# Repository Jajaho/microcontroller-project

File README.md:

# Projekt Mikrocontroller
Layout and Source code files.  
Uses the PlatformIO IDE in VSCode.  
## Useful links
[C++ Formatter](https://codebeautify.org/cpp-formatter-beautifier)

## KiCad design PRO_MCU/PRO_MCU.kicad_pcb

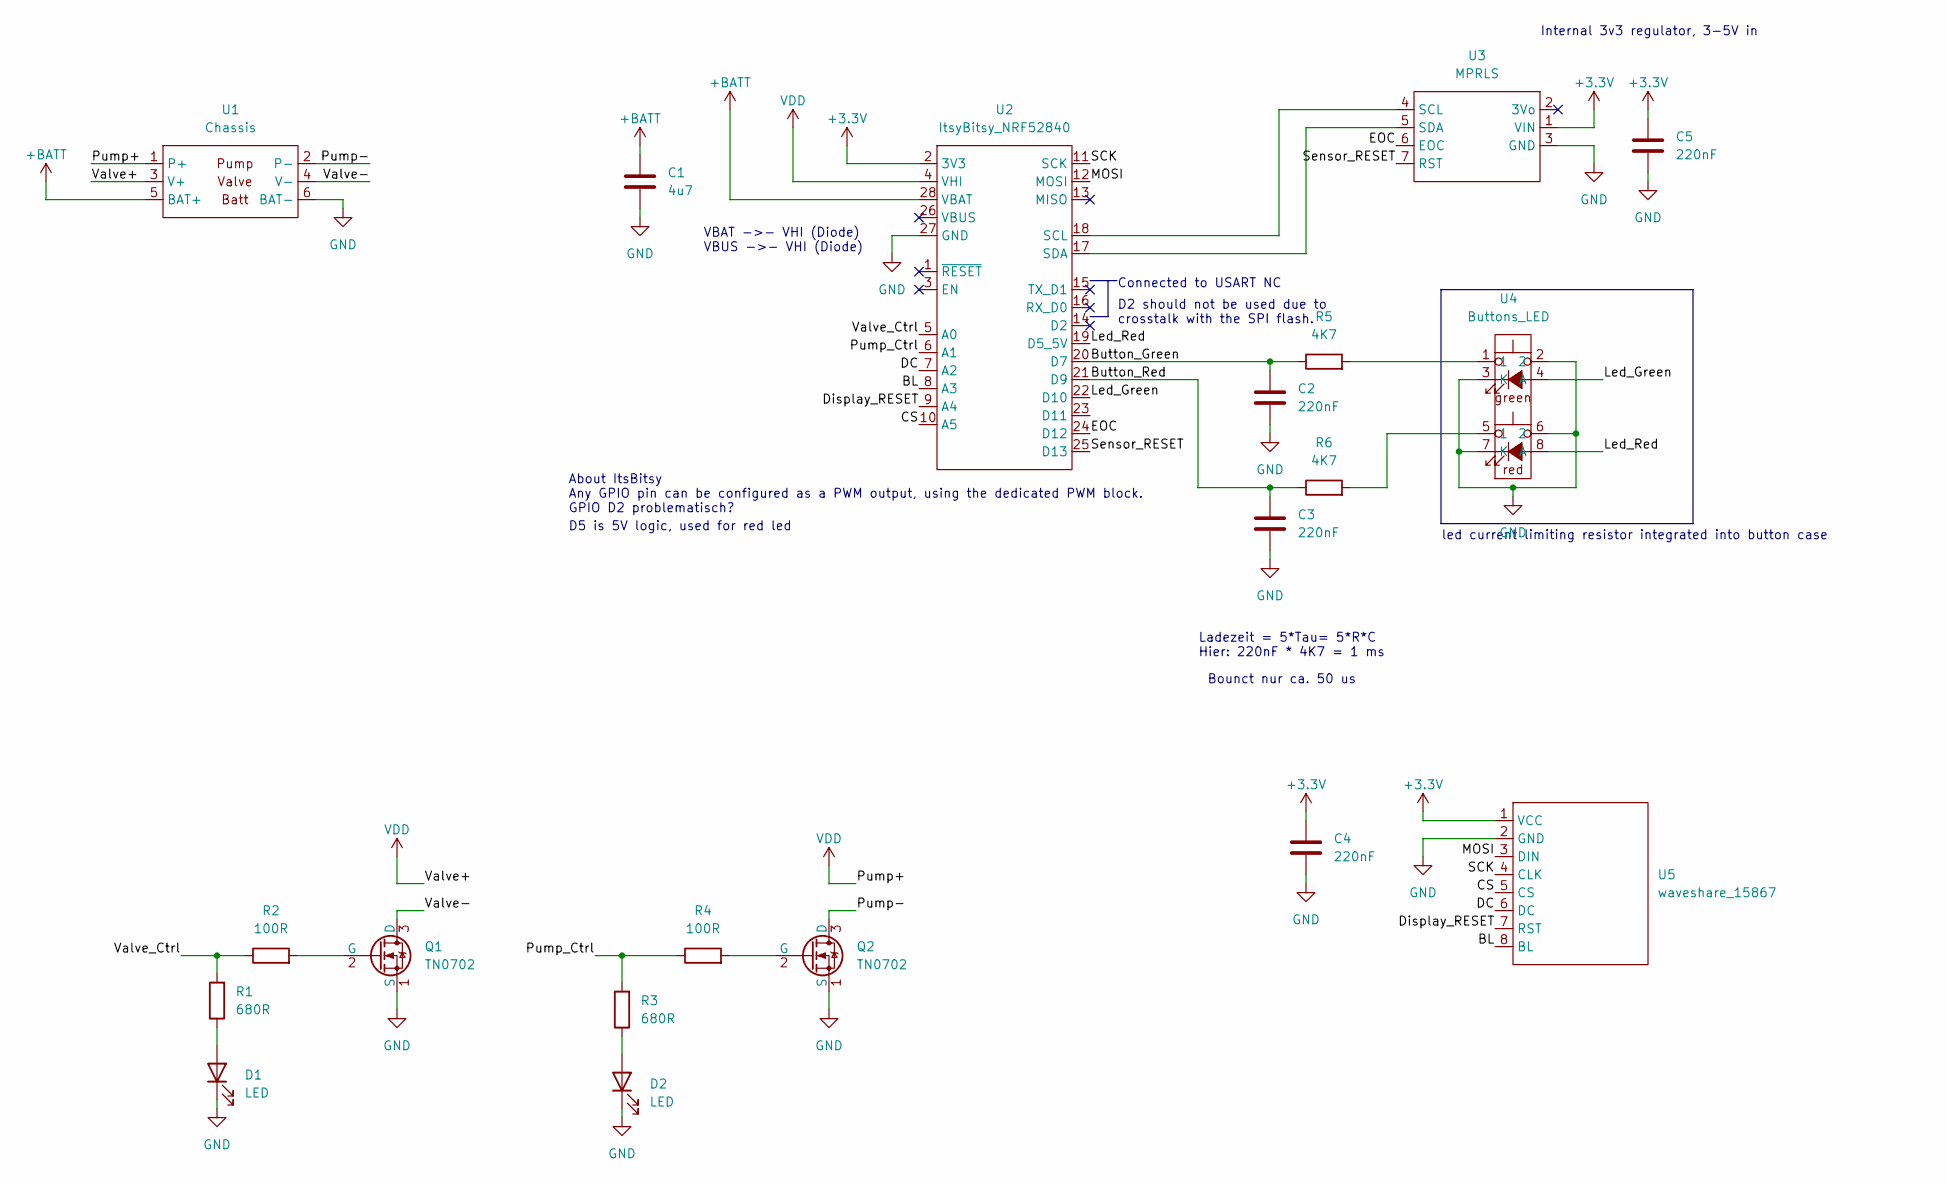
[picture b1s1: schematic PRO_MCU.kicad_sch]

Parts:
C1: 4u7; C_0805_2012Metric_Pad1.18x1.45mm_HandSolder
C2, C3, C4, C5: 220nF; C_0805_2012Metric_Pad1.18x1.45mm_HandSolder
D1, D2: LED; LED_D3.0mm
Q1, Q2: TN0702; TO-92
R1, R3: 680R; R_Axial_DIN0207_L6.3mm_D2.5mm_P10.16mm_Horizontal
R2, R4: 100R; R_Axial_DIN0207_L6.3mm_D2.5mm_P10.16mm_Horizontal
R5, R6: 4K7; R_Axial_DIN0207_L6.3mm_D2.5mm_P10.16mm_Horizontal
U1: Chassis; IDC-Header_2x03_P2.54mm_Vertical
U2: ItsyBitsy_NRF52840
U3: MPRLS
U4: Buttons_LED; IDC-Header_2x04_P2.54mm_Vertical
U5: waveshare_15867; IDC-Header_2x04_P2.54mm_Vertical

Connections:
+3.3V: C4.1, C5.1, U2.2 (3V3), U3.1 (VIN), U5.1 (VCC)
+BATT: C1.1, U1.5 (BAT+), U2.28 (VBAT)
/BL: U2.8 (A3), U5.8 (BL)
/Button_Green: C2.1, R5.1, U2.20 (D7)
/Button_Red: C3.1, R6.1, U2.21 (D9)
/CS: U2.10 (A5), U5.5 (CS)
/DC: U2.7 (A2), U5.6 (DC)
/Display_RESET: U2.9 (A4), U5.7 (RST)
/EOC: U2.24 (D12), U3.6 (EOC)
/Led_Green: U2.22 (D10), U4.4 (A)
/Led_Red: U2.19 (D5_5V), U4.8 (A)
/MOSI: U2.12 (MOSI), U5.3 (DIN)
/Pump-: Q2.3 (D), U1.2 (P-)
/Pump_Ctrl: R3.2, R4.1, U2.6 (A1)
/SCK: U2.11 (SCK), U5.4 (CLK)
/Sensor_RESET: U2.25 (D13), U3.7 (RST)
/Valve-: Q1.3 (D), U1.4 (V-)
/Valve_Ctrl: R1.2, R2.1, U2.5 (A0)
GND: C1.2, C2.2, C3.2, C4.2, C5.2, D1.1 (K), D2.1 (K), Q1.1 (S), Q2.1 (S), U1.6 (BAT-), U2.27 (GND), U3.3 (GND), U4.2, U4.3 (K), U4.6 (2), U4.7 (K), U5.2 (GND)
unnamed: D1.2 (A), R1.1
unnamed: D2.2 (A), R3.1
unnamed: Q1.2 (G), R2.2
unnamed: Q2.2 (G), R4.2
unnamed: R5.2, U4.1
unnamed: R6.2, U4.5 (1)
unnamed: U2.18 (SCL), U3.4 (SCL)
unnamed: U2.17 (SDA), U3.5 (SDA)
VDD: U1.1 (P+), U1.3 (V+), U2.4 (VHI)

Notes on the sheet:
Connected to USART NC
About ItsBitsy Any GPIO pin can be configured as a PWM output, using the dedicated PWM block. GPIO D2 problematisch?
Bounct nur ca. 50 us
VBAT ->- VHI (Diode) VBUS ->- VHI (Diode)
led current limiting resistor integrated into button case
Internal 3v3 regulator, 3-5V in
D2 should not be used due to crosstalk with the SPI flash.
Ladezeit = 5*Tau= 5*R*C Hier: 220nF * 4K7 = 1 ms
D5 is 5V logic, used for red led

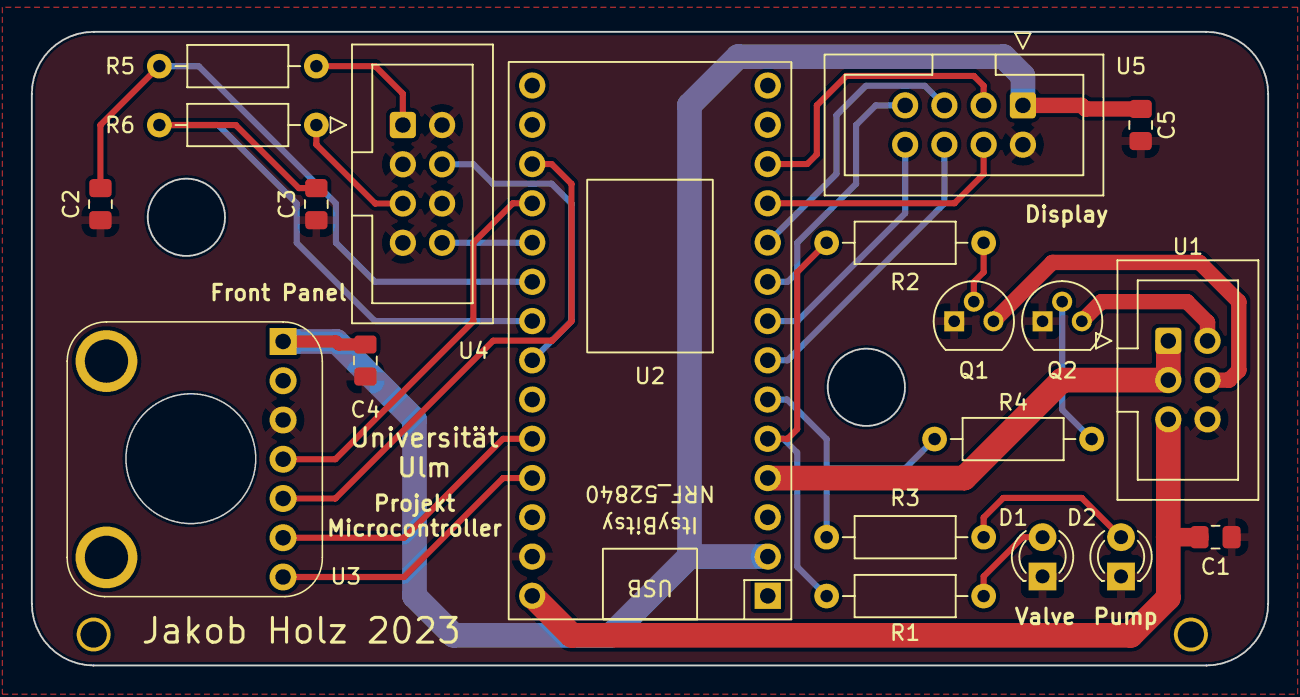
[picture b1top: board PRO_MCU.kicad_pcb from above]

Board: 2 copper layers, 80.0 x 41.0 mm, 21 parts (1 on the bottom side), 28 nets.

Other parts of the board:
Logo: BoardGeometry

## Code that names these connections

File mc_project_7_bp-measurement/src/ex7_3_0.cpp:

#include <Arduino.h>
#include <Adafruit_TinyUSB.h> // for Serial
#include <Wire.h>
#include "Adafruit_MPRLS.h"
#include <SPI.h>
#include <math.h>
#include "SdFat.h"
#include "Adafruit_SPIFlash.h"

#define RESET_PIN -1 // set to any GPIO pin # to hard-reset on begin()
#define EOC 12 // set to any GPIO pin to read end-of-conversion by pin

#define LED_RED 5
#define LED_GREEN 10
#define BTN_RED 9
#define BTN_GREEN 7

#define VALVE A0
#define PUMP A1

#define pressureIncrease 280 //put this value to 240+40 as overshoot compensation if you want to measure the blood pressure
#define pressureThreshold 40 //lower threshold, when the cuff is deflated,put this value to 40 for blood pressure measurement

#define settleTime 500 //settle time in ms, when pump/valve is turned on/off
#define maxTime 120000 //after 2 minutes stop the measurement
#define measPeriod 10 //10ms of sampling time
#define HPnominator_5Hz 0.864244751836367 //filter coefficient of the nominator of the highpass filter, with f_3dB = 5Hz
#define HPdenominator_5Hz 0.728489503672734 //filter coefficient of the denominator of the highpass filter, with f_3dB = 5Hz
#define HPnominator_0_5Hz 0.984534960996653 //filter coefficient of the nominator of the highpass filter, with f_3dB = 0.5Hz
#define HPdenominator_0_5Hz 0.969069921993306 //filter coefficient of the denominator of the highpass filter, with f_3dB = 0.5Hz

//Library object for the flash configuration
Adafruit_FlashTransport_QSPI flashTransport;
Adafruit_SPIFlash flash(&flashTransport);

// file system object from SdFat
FatVolume fatfs; //file system
File32 myFile; //file format for the SD memory
int readFile; //read the file position, ATTENTION: Output is decoded as integer in ASCII-format!

//Library for the pressure sensor
Adafruit_MPRLS pressureSensor = Adafruit_MPRLS();
float currentPressure[2]; //intermediate pressure values, with buffer of last value
float startPressure = 0; //intermediate pressure values

volatile bool flagInterrupt = false; //emergency flag from the interrupt
volatile bool pumpFlag = false; //flag for the pump control

unsigned long startTimer = 0; //startpoint of the timer
unsigned long endTimer = 0; //endpoint of the timer
unsigned long timeStamp = 0; //timestamp of the current measurement
unsigned long startMaxTimer = 0; //start the timer at the beginning of the whole measurement process, to have a maximum time to stop

float HPbuffer_5Hz[2]; //buffer of last two highpass filter values, with f_3dB = 5Hz
float HPbuffer_0_5Hz[2]; //buffer of last two highpass filter values, with f_3dB = 0.5Hz

uint16_t measSample[12000]; //array for the measured samples, maximum 2 minutes every 10ms -> 12000 entries
int16_t HPmeasSample[12000]; //array of the highpass filtered samples
int writeCount = 0; //used for print counter every 500ms and position in array to write to


// ----------------------- Function prototypes ----------------------- //
//Interrupt function
void interruptFunction();

void setup() {

  // -----  Inputs  -------- //
  pinMode(BTN_RED, INPUT_PULLUP);   // Button is active low!
  pinMode(BTN_GREEN, INPUT_PULLUP); // Button is active low!

  // -----  Outputs  -------- //
  // LEDs:
  pinMode(LED_GREEN, OUTPUT);
  digitalWrite(LED_GREEN, LOW);

  pinMode(LED_RED, OUTPUT);
  digitalWrite(LED_RED, LOW);

  // ----- Actuators --------- //
  pinMode(VALVE, OUTPUT);
  digitalWrite(VALVE, HIGH);

  pinMode(PUMP, OUTPUT);   
  digitalWrite(PUMP, LOW);

  attachInterrupt(digitalPinToInterrupt(BTN_RED), panicISR, FALLING);
  //attachInterrupt(digitalPinToInterrupt(BTN_GREEN), pumpControlISR, FALLING);

  //start serial communication and set baud rate
  Serial.begin(9600);
  Serial.println("MPRLS Simple Test");

  if (!pressureSensor.begin()) {
    Serial.println("Failed to communicate with MPRLS sensor, check wiring?");
    while (1) {
    delay(10);
    }
  }
  Serial.println("Found MPRLS sensor");
  Serial.println("Initializing Filesystem on external flash...");

  // Init external flash
  flash.begin();

  // Open file system on the flash
  if (!fatfs.begin(&flash)) {
    Serial.println("Error: filesystem is not existed. Please try SdFat_format example to make one.");
    while (1) {
    delay(10);
    }
  }

  Serial.println("initialization done.");
  //pinMode(BTN_GREEN, INPUT_PULLUP);
  //pinMode(BTN_RED, INPUT_PULLUP);
  //attachInterrupt(digitalPinToInterrupt(interruptButton), interruptFunction, CHANGE);
  //pinMode(PUMP, OUTPUT);
  //digitalWrite(PUMP, LOW);
  //pinMode(VALVE, OUTPUT);
  //digitalWrite(VALVE, LOW);

}

void loop() {
  //refresh memory of sample-buffer
  memset(currentPressure, 0, sizeof(currentPressure));
  memset(measSample, 0, sizeof(measSample));
  memset(HPbuffer_5Hz, 0, sizeof(HPbuffer_5Hz));
  memset(HPbuffer_0_5Hz, 0, sizeof(HPbuffer_0_5Hz));
  memset(HPmeasSample, 0, sizeof(HPmeasSample));
  writeCount = 0;
  Serial.println("Press the green button to start!");
  
  while (digitalRead(BTN_GREEN) == HIGH) {}

  flagInterrupt = false;

  // PUT YOUR CODE HERE 

  startTimer = millis();
  endTimer = startTimer + maxTime;
  startPressure = pressureSensor.readPressure();
  while (millis() < endTimer)
  {

    timeStamp = millis();
    if (timeStamp - startTimer >= measPeriod) {
      if (pumpFlag) {
        digitalWrite(VALVE, LOW);
        delay(6);
      }
      
      startTimer = timeStamp; // set the timestamp of the current measurement

      pressure_hPa = pressureSensor.readPressure();
    }
  }
  
  
  
  //write measurement array to a .txt file
  if (!flagInterrupt) {
    fatfs.remove("pressureMeasurement.txt");
    myFile = fatfs.open("pressureMeasurement.txt", FILE_WRITE);
    if (myFile) {
      Serial.print("Writing to pressureMeasurement.txt...");
      for (int i = 0; i < sizeof(measSample) / 2; i++) {
        myFile.print(measSample[i]);
        myFile.print(",");
      }
      myFile.close();
      Serial.println("done!");
    } else {
        Serial.println("error opening pressureTest.txt");
    }

    fatfs.remove("HPpressureMeasurement.txt");
    myFile = fatfs.open("HPpressureMeasurement.txt", FILE_WRITE);

    if (myFile) {
      Serial.print("Writing to HPpressureMeasurement.txt...");
      for (int i = 0; i < sizeof(measSample) / 2; i++) {
        myFile.print(HPmeasSample[i]);
        myFile.print(",");
      }
      myFile.close();
      Serial.println("done!");
    } else {
      Serial.println("error opening pressureTest.txt");
    }
  }
}


void panicISR() {
  digitalWrite(VALVE, LOW);
  digitalWrite(PUMP, LOW);
  flagInterrupt = true;
}


//function of the highpass filter
void HPfilter(float* pressure, float* HP_5Hz, float* HP_0_5Hz) {
  *(HP_5Hz + 1) = *(HP_5Hz); //Shift buffer
  *(HP_0_5Hz + 1) = *(HP_0_5Hz); //Shift buffer

  //Highpass filter in time domain
  *(HP_5Hz) = HPnominator_5Hz * (*(pressure) - *(pressure + 1)) +
  HPdenominator_5Hz * (*(HP_5Hz + 1));
  *(HP_0_5Hz) = HPnominator_0_5Hz * (*(HP_5Hz) - *(HP_5Hz + 1)) +
  HPdenominator_0_5Hz * (*(HP_0_5Hz + 1));
}

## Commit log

2023-04-24 Adds .gitignore
2023-04-24 Adds PIO project
2023-04-24 Updated KiCad project [After review]
2023-04-24 Adds KiCad project [Before review]
2023-05-08 Adds test code
    wrong pin defs
2023-05-09 Adds display EOC port
    swaps some other pins around
2023-05-09 Updated port definitions
    removes 100 ms delay from main loop
2023-05-15 Updates schematic symbols,, revised debouncing
    - Updates electrical types of symbols in library
2023-05-15 Adds kicad_pcb for older KiCAD version
2023-05-15 Updates project to KiCAD 7.0
2023-05-15 Updates layout, schematic, symbols and footprints
    - Adds rounded corners to board geometry
    - Component placement
    - Modifications to schematic to make routing easier
2023-05-15 Updates power net labels to KiCAD 7.0 (resolves warnings)
2023-05-15 V1.0 Fabrication
2023-05-22 Moves test to mc_project_3_breadboard Adds mc_project_5_baremetal
2023-05-22 Renames gpio_func_c to utility.cpp
2023-05-22 Adds bool GPIO_get_Input()
2023-05-22 Adds GPIO_set_Input_Pullup
2023-05-22 Adds faulty libs for final task of day 5
2023-05-22 Auto stash before merge of "master" and "origin/master"
2023-06-05 c_cpp_properties
2023-06-05 Adds project_6
2023-06-05 project_6 task 2.1 complete
2023-06-05 Adds panic functionality with big red button
2023-06-05 task project_6 3.2 done
2023-06-05 Adds display hello world (mc_project_6 task 4)
2023-06-05 mc_project_6 task 6 complete
2023-06-05 Adds flash.cpp
2023-06-12 created exercise 7 folder from ex 6 renamed first lab folder
2023-06-12 Compied project example code from manual
2023-06-12 mc_project_7 exercise 3 template
2023-06-12 Adds mc_project_7 exercise 3.1 template code
2023-06-12 Adds HPpreasureData
2023-06-12 Moves ex3.1 to main for testing
2023-06-12 Adds mass_storage.pp
2023-06-12 Exchanges SdFat depedency with platformIO fork
2023-06-12 Edits platformio.ini envs
2023-06-12 Adds mass_storage.cpp back
2023-06-12 Adds readme to exercise 7
2023-06-12 Adds ex7_4_1.cpp template (unedited)
2023-06-12 Adds ex7_4_2.cpp template (unedited)
2023-06-12 Adds ex7_5_0.cpp template (unedited)
2023-06-12 Updates ex7_3_0.cpp to look nicer
2023-06-12 Adds ex7_6_2.cpp template (unedited)
2023-06-12 Updates readme
2023-06-13 Updates ex6
2023-06-13 Started implementing 2 min measurement to ex3_0
2023-06-21 Adds Student_files_help
2023-06-21 Adds Student_file_help files to new dev projects
2023-06-21 Adds dependencies to dev
2023-06-26 pins
2023-06-26 fixes project 6 dependencies
2023-06-26 Adds heart rate calculation
2023-06-26 dev_8 fixed wrong mcu selection in platformio.ini
2023-06-26 Worked on heartbeat measurement in test.cpp
2023-06-28 worked on heartrate
2023-06-28 heartrate calculation in test.cpp working!
2023-06-30 Adds matlab debug programms
2023-06-30 Removed int16_t * read_file(String filename)
    because it was faulty and different function could replace it
2023-07-01 worked on serial readout matlab script
2023-07-03 Adds mass_storage.cpp to mc_project_8_dev
2023-07-03 Wroked on matlab uart com
2023-07-07 Add new matlab serial com script
2023-07-10 Adds calcHeartbeat to mc_project 7
2023-07-12 Finish
